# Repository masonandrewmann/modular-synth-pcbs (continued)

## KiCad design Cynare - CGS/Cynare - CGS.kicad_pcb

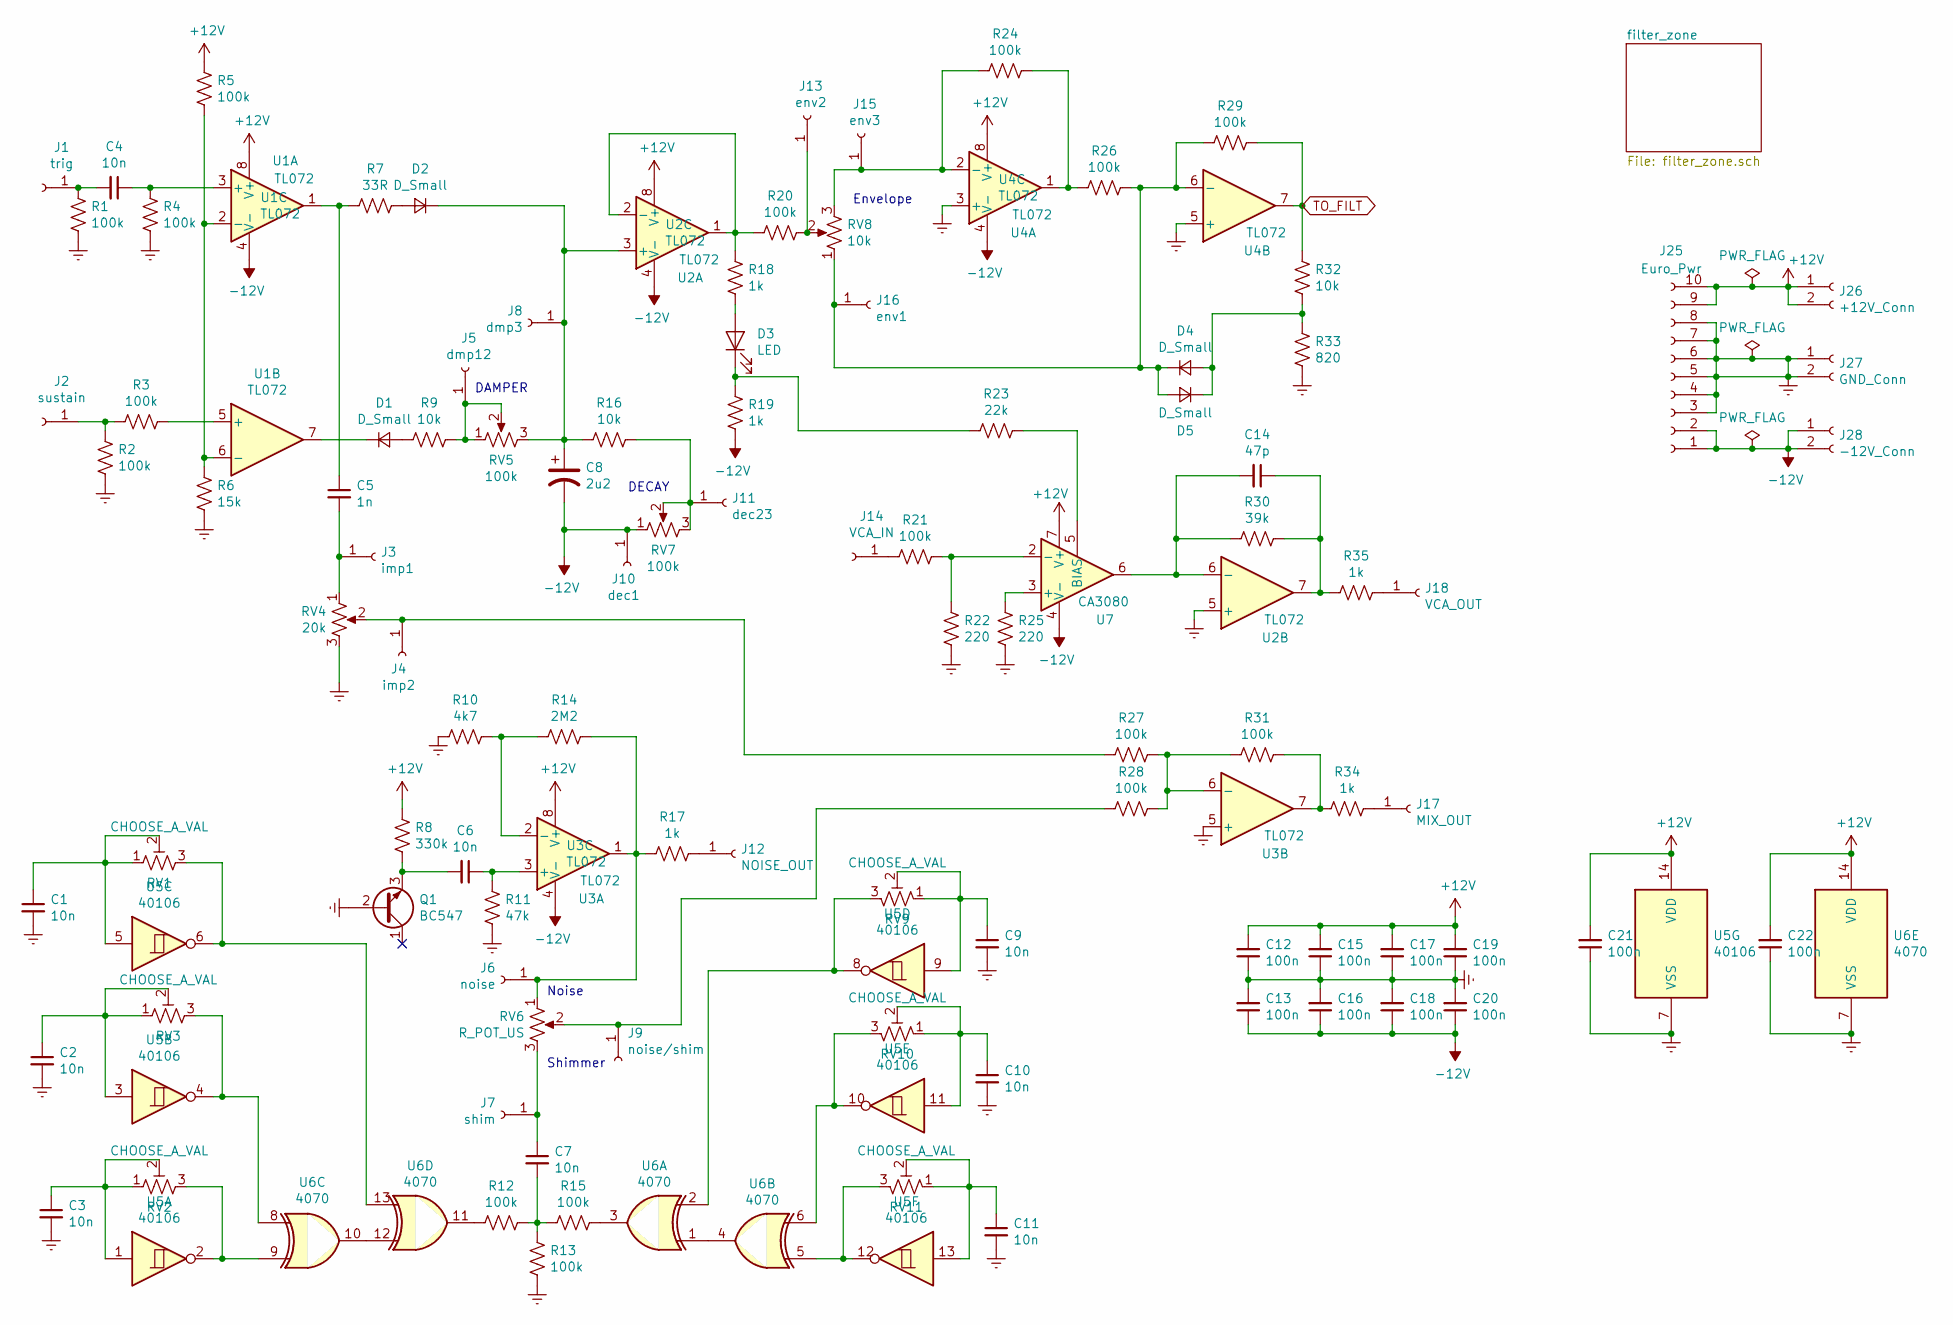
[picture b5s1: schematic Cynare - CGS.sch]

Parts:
C1, C2, C3, C4, C6, C7, C9, C10, C11: 10n; C_Rect_L7.0mm_W2.5mm_P5.00mm
C5: 1n; C_Rect_L7.0mm_W2.5mm_P5.00mm
C8: 2u2; CP_Radial_D5.0mm_P2.00mm
C12, C13, C15, C16, C17, C18, C19, C20, C21, C22: 100n; C_Rect_L7.0mm_W2.5mm_P5.00mm
C14: 47p; C_Rect_L7.0mm_W2.5mm_P5.00mm
D1, D2, D4, D5: D_Small; D_T-1_P5.08mm_Horizontal
D3: LED; LED_D4.0mm
J1: trig; SolderWirePad_1x01_Drill1mm
J2: sustain; SolderWirePad_1x01_Drill1mm
J3: imp1; SolderWirePad_1x01_Drill1mm
J4: imp2; SolderWirePad_1x01_Drill1mm
J5: dmp12; SolderWirePad_1x01_Drill1mm
J6: noise; SolderWirePad_1x01_Drill1mm
J7: shim; SolderWirePad_1x01_Drill1mm
J8: dmp3; SolderWirePad_1x01_Drill1mm
J9: noise/shim; SolderWirePad_1x01_Drill1mm
J10: dec1; SolderWirePad_1x01_Drill1mm
J11: dec23; SolderWirePad_1x01_Drill1mm
J12: NOISE_OUT; SolderWirePad_1x01_Drill1mm
J13: env2; SolderWirePad_1x01_Drill1mm
J14: VCA_IN; SolderWirePad_1x01_Drill1mm
J15: env3; SolderWirePad_1x01_Drill1mm
J16: env1; SolderWirePad_1x01_Drill1mm
J17: MIX_OUT; SolderWirePad_1x01_Drill1mm
J18: VCA_OUT; SolderWirePad_1x01_Drill1mm
J25: Euro_Pwr; IDC-Header_2x05_P2.54mm_Vertical
J26: +12V_Conn; SolderWirePad_1x02_P3.81mm_Drill1mm
J27: GND_Conn; SolderWirePad_1x02_P3.81mm_Drill1mm
J28: -12V_Conn; SolderWirePad_1x02_P3.81mm_Drill1mm
Q1: BC547; TO-92_Inline_Wide
R1, R2, R3, R4, R5, R12, R13, R15, R20, R21, R24, R26, R27, R28, R29, R31: 100k; R_Axial_DIN0207_L6.3mm_D2.5mm_P7.62mm_Horizontal
R6: 15k; R_Axial_DIN0207_L6.3mm_D2.5mm_P7.62mm_Horizontal
R7: 33R; R_Axial_DIN0207_L6.3mm_D2.5mm_P7.62mm_Horizontal
R8: 330k; R_Axial_DIN0207_L6.3mm_D2.5mm_P7.62mm_Horizontal
R9, R16, R32: 10k; R_Axial_DIN0207_L6.3mm_D2.5mm_P7.62mm_Horizontal
R10: 4k7; R_Axial_DIN0207_L6.3mm_D2.5mm_P7.62mm_Horizontal
R11: 47k; R_Axial_DIN0207_L6.3mm_D2.5mm_P7.62mm_Horizontal
R14: 2M2; R_Axial_DIN0207_L6.3mm_D2.5mm_P7.62mm_Horizontal
R17, R18, R19, R34, R35: 1k; R_Axial_DIN0207_L6.3mm_D2.5mm_P7.62mm_Horizontal
R22, R25: 220; R_Axial_DIN0207_L6.3mm_D2.5mm_P7.62mm_Horizontal
R23: 22k; R_Axial_DIN0207_L6.3mm_D2.5mm_P7.62mm_Horizontal
R30: 39k; R_Axial_DIN0207_L6.3mm_D2.5mm_P7.62mm_Horizontal
R33: 820; R_Axial_DIN0207_L6.3mm_D2.5mm_P7.62mm_Horizontal
RV1, RV2, RV3, RV9, RV10, RV11: CHOOSE_A_VAL; Potentiometer_Runtron_RM-065_Vertical
RV4: 20k
RV5, RV7: 100k
RV6: R_POT_US
RV8: 10k
U1, U2, U3, U4: TL072; DIP-8_W7.62mm_Socket
U5: 40106; DIP-14_W7.62mm_Socket
U6: 4070; DIP-14_W7.62mm_Socket
U7: CA3080; DIP-8_W7.62mm_Socket

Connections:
+12V: C12.2, C15.2, C17.2, C19.2, C21.2, C22.2, J25.9, J25.10, J26.1, J26.2, R5.1, R8.2, U1.8 (V+), U2.8 (V+), U3.8 (V+), U4.8 (V+), U5.14 (VDD), U6.14 (VDD), U7.7 (V+); also elsewhere on the board
-12V: C8.2, C13.1, C16.1, C18.1, C20.1, J10.1, J25.1, J25.2, J28.1, J28.2, R19.1, RV7.1, U1.4 (V-), U2.4 (V-), U3.4 (V-), U4.4 (V-), U7.4 (V-); also elsewhere on the board
Earth: C1.2, C2.2, C3.2, C9.2, C10.2, C11.2, C12.1, C13.2, C15.1, C16.2, C17.1, C18.2, C19.1, C20.2, C21.1, C22.1, J25.3, J25.4, J25.5, J25.6, J25.7, J25.8, J27.1, J27.2, Q1.2 (B), R1.2, R2.1, R4.2, R6.1, R10.2, R11.1, R13.1, R22.1, R25.1, R33.1, RV4.3, U2.5 (+), U3.5 (+), U4.3 (+), U4.5 (+), U5.7 (VSS), U6.7 (VSS); also elsewhere on the board
unnamed: C1.1, RV1.1, RV1.2, U5.5
unnamed: C2.1, RV3.1, RV3.2, U5.3
unnamed: C3.1, RV2.1, RV2.2, U5.1
unnamed: C4.1, R4.1, U1.3 (+)
unnamed: C4.2, J1.1, R1.1
unnamed: C5.1, R7.2, U1.1
unnamed: C5.2, J3.1, RV4.1
unnamed: C6.1, R11.2, U3.3 (+)
unnamed: C6.2, Q1.3 (E), R8.1
unnamed: C7.1, J7.1, RV6.3
unnamed: C7.2, R12.1, R13.2, R15.1
unnamed: C8.1, D2.1 (K), J8.1, R16.2, RV5.3, U2.3 (+)
unnamed: C9.1, RV9.1, RV9.2, U5.9
unnamed: C10.1, RV10.1, RV10.2, U5.11
unnamed: C11.1, RV11.1, RV11.2, U5.13
unnamed: C14.1, R30.2, R35.1, U2.7
unnamed: C14.2, R30.1, U2.6 (-), U7.6
unnamed: D1.1 (K), U1.7
unnamed: D1.2 (A), R9.2
unnamed: D2.2 (A), R7.1
unnamed: D3.1 (K), R19.2, R23.1
unnamed: D3.2 (A), R18.1
unnamed: D4.1 (K), D5.2 (A), J16.1, R26.1, R29.2, RV8.1, U4.6 (-)
unnamed: D4.2 (A), D5.1 (K), R32.1, R33.2
unnamed: J2.1, R2.2, R3.2
unnamed: J4.1, R27.1, RV4.2
unnamed: J5.1, R9.1, RV5.1, RV5.2
unnamed: J6.1, R14.1, R17.2, RV6.1, U3.1
unnamed: J9.1, R28.1, RV6.2
unnamed: J11.1, R16.1, RV7.2, RV7.3
unnamed: J12.1, R17.1
unnamed: J13.1, R20.1, RV8.2
unnamed: J14.1, R21.1
unnamed: J15.1, R24.2, RV8.3, U4.2 (-)
unnamed: J17.1, R34.2
unnamed: J18.1, R35.2
unnamed: R3.1, U1.5 (+)
unnamed: R5.2, R6.2, U1.2 (-), U1.6 (-)
unnamed: R10.1, R14.2, U3.2 (-)
unnamed: R12.2, U6.11
unnamed: R15.2, U6.3
unnamed: R18.2, R20.2, U2.1, U2.2 (-)
unnamed: R21.2, R22.2, U7.2 (-)
unnamed: R23.2, U7.5 (BIAS)
unnamed: R24.1, R26.2, U4.1
unnamed: R25.2, U7.3 (+)
unnamed: R27.2, R28.2, R31.1, U3.6 (-)
unnamed: R31.2, R34.1, U3.7
unnamed: RV1.3, U5.6, U6.13
unnamed: RV2.3, U5.2, U6.9
unnamed: RV3.3, U5.4, U6.8
unnamed: RV9.3, U5.8, U6.2
unnamed: RV10.3, U5.10, U6.6
unnamed: RV11.3, U5.12, U6.5
unnamed: U6.1, U6.4
unnamed: U6.10, U6.12
TO_FILT: R29.1, R32.2, U4.7; also elsewhere on the board

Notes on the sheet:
DAMPER
DECAY
Noise
Shimmer
Envelope

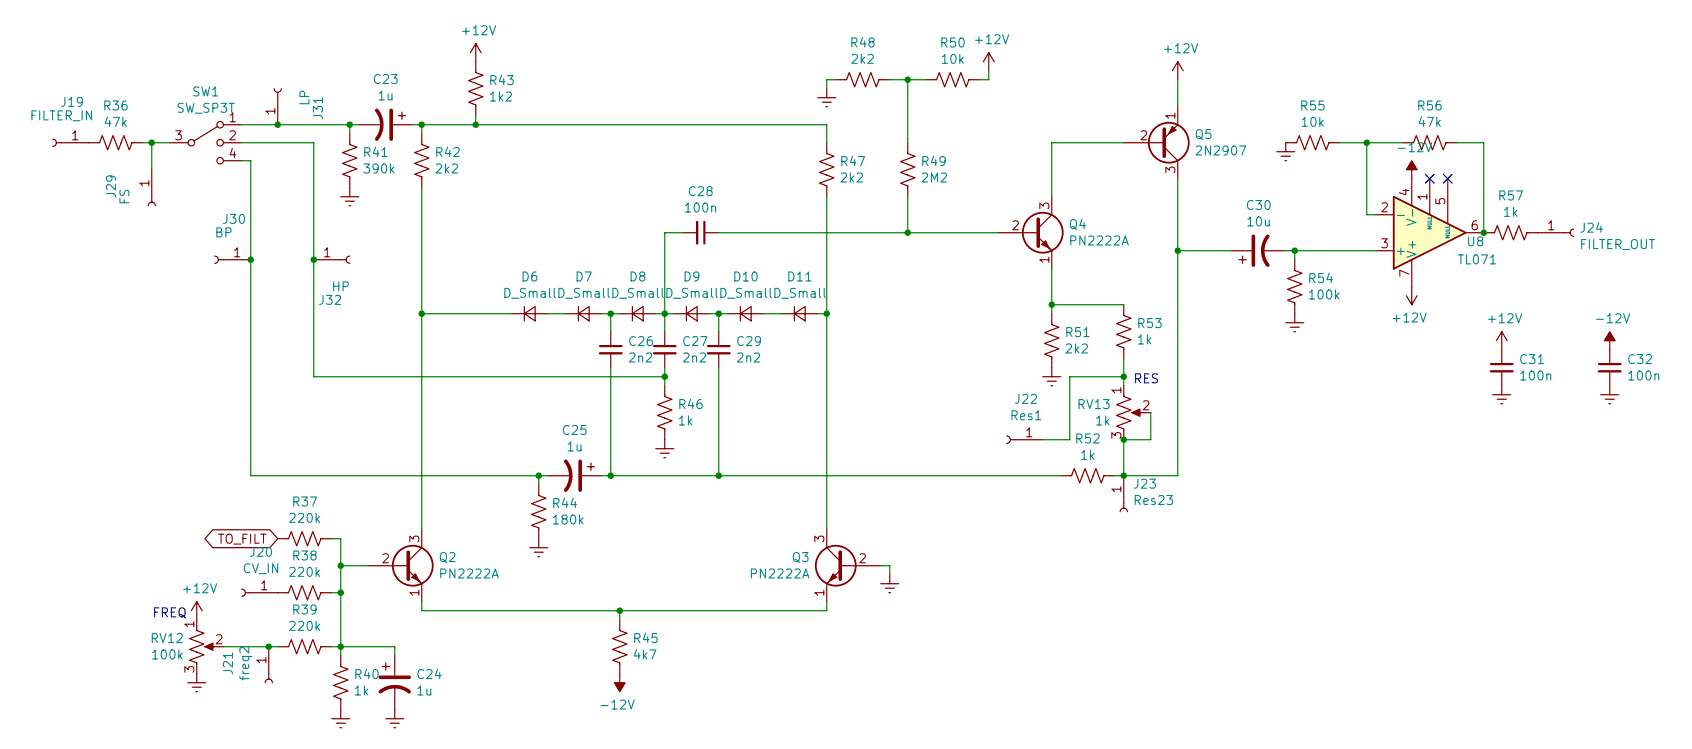
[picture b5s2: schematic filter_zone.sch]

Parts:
C23, C24, C25: 1u; CP_Radial_D5.0mm_P2.50mm
C26, C27, C29: 2n2; C_Rect_L7.0mm_W2.5mm_P5.00mm
C28: 100n; C_Rect_L7.0mm_W2.5mm_P5.00mm
C30: 10u; CP_Radial_D5.0mm_P2.50mm
C31, C32: 100n; C_0603_1608Metric_Pad1.05x0.95mm_HandSolder
D6, D7, D8, D9, D10, D11: D_Small; D_T-1_P5.08mm_Horizontal
J19: FILTER_IN; SolderWirePad_1x01_Drill1mm
J20: CV_IN; SolderWirePad_1x01_Drill1mm
J21: freq2; SolderWirePad_1x01_Drill1mm
J22: Res1; SolderWirePad_1x01_Drill1mm
J23: Res23; SolderWirePad_1x01_Drill1mm
J24: FILTER_OUT; SolderWirePad_1x01_Drill1mm
J29: FS; SolderWirePad_1x01_Drill1mm
J30: BP; SolderWirePad_1x01_Drill1mm
J31: LP; SolderWirePad_1x01_Drill1mm
J32: HP; SolderWirePad_1x01_Drill1mm
Q2, Q3, Q4: PN2222A; TO-92_Inline_Wide
Q5: 2N2907; TO-92_Inline_Wide
R36, R56: 47k; R_Axial_DIN0207_L6.3mm_D2.5mm_P7.62mm_Horizontal
R37, R38, R39: 220k; R_Axial_DIN0207_L6.3mm_D2.5mm_P7.62mm_Horizontal
R40, R46, R52, R53, R57: 1k; R_Axial_DIN0207_L6.3mm_D2.5mm_P7.62mm_Horizontal
R41: 390k; R_Axial_DIN0207_L6.3mm_D2.5mm_P7.62mm_Horizontal
R42, R47, R48, R51: 2k2; R_Axial_DIN0207_L6.3mm_D2.5mm_P7.62mm_Horizontal
R43: 1k2; R_Axial_DIN0207_L6.3mm_D2.5mm_P7.62mm_Horizontal
R44: 180k; R_Axial_DIN0207_L6.3mm_D2.5mm_P7.62mm_Horizontal
R45: 4k7; R_Axial_DIN0207_L6.3mm_D2.5mm_P7.62mm_Horizontal
R49: 2M2; R_Axial_DIN0207_L6.3mm_D2.5mm_P7.62mm_Horizontal
R50, R55: 10k; R_Axial_DIN0207_L6.3mm_D2.5mm_P7.62mm_Horizontal
R54: 100k; R_Axial_DIN0207_L6.3mm_D2.5mm_P7.62mm_Horizontal
RV12: 100k
RV13: 1k
SW1: SW_SP3T
U8: TL071; DIP-8_W7.62mm_Socket

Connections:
+12V: C31.1, Q5.1 (E), R43.2, R50.2, RV12.1, U8.7 (V+); also elsewhere on the board
-12V: C32.1, R45.1, U8.4 (V-); also elsewhere on the board
Earth: C24.2, C31.2, C32.2, Q3.2 (B), R40.2, R41.1, R44.1, R46.1, R48.1, R51.2, R54.2, R55.2, RV12.3; also elsewhere on the board
unnamed: C23.1, R42.2, R43.1, R47.2
unnamed: C23.2, J31.1, R41.2, SW1.1
unnamed: C24.1, Q2.2 (B), R37.2, R38.2, R39.2, R40.1
unnamed: C25.1, C26.2, C29.2, R52.2
unnamed: C25.2, J30.1, R44.2, SW1.4
unnamed: C26.1, D7.2 (A), D8.1 (K)
unnamed: C27.1, C28.2, D8.2 (A), D9.1 (K)
unnamed: C27.2, J32.1, R46.2, SW1.2
unnamed: C28.1, Q4.2 (B), R49.1
unnamed: C29.1, D9.2 (A), D10.1 (K)
unnamed: C30.1, J23.1, Q5.3 (C), R52.1, RV13.2, RV13.3
unnamed: C30.2, R54.1, U8.3 (+)
unnamed: D6.1 (K), Q2.3 (C), R42.1
unnamed: D6.2 (A), D7.1 (K)
unnamed: D10.2 (A), D11.1 (K)
unnamed: D11.2 (A), Q3.3 (C), R47.1
unnamed: J19.1, R36.2
unnamed: J20.1, R38.1
unnamed: J21.1, R39.1, RV12.2
unnamed: J22.1, R53.2, RV13.1
unnamed: J24.1, R57.1
unnamed: J29.1, R36.1, SW1.3
unnamed: Q2.1 (E), Q3.1 (E), R45.2
unnamed: Q4.1 (E), R51.1, R53.1
unnamed: Q4.3 (C), Q5.2 (B)
unnamed: R48.2, R49.2, R50.1
unnamed: R55.1, R56.2, U8.2 (-)
unnamed: R56.1, R57.2, U8.6
TO_FILT: R37.1; also elsewhere on the board

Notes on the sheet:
RES
FREQ

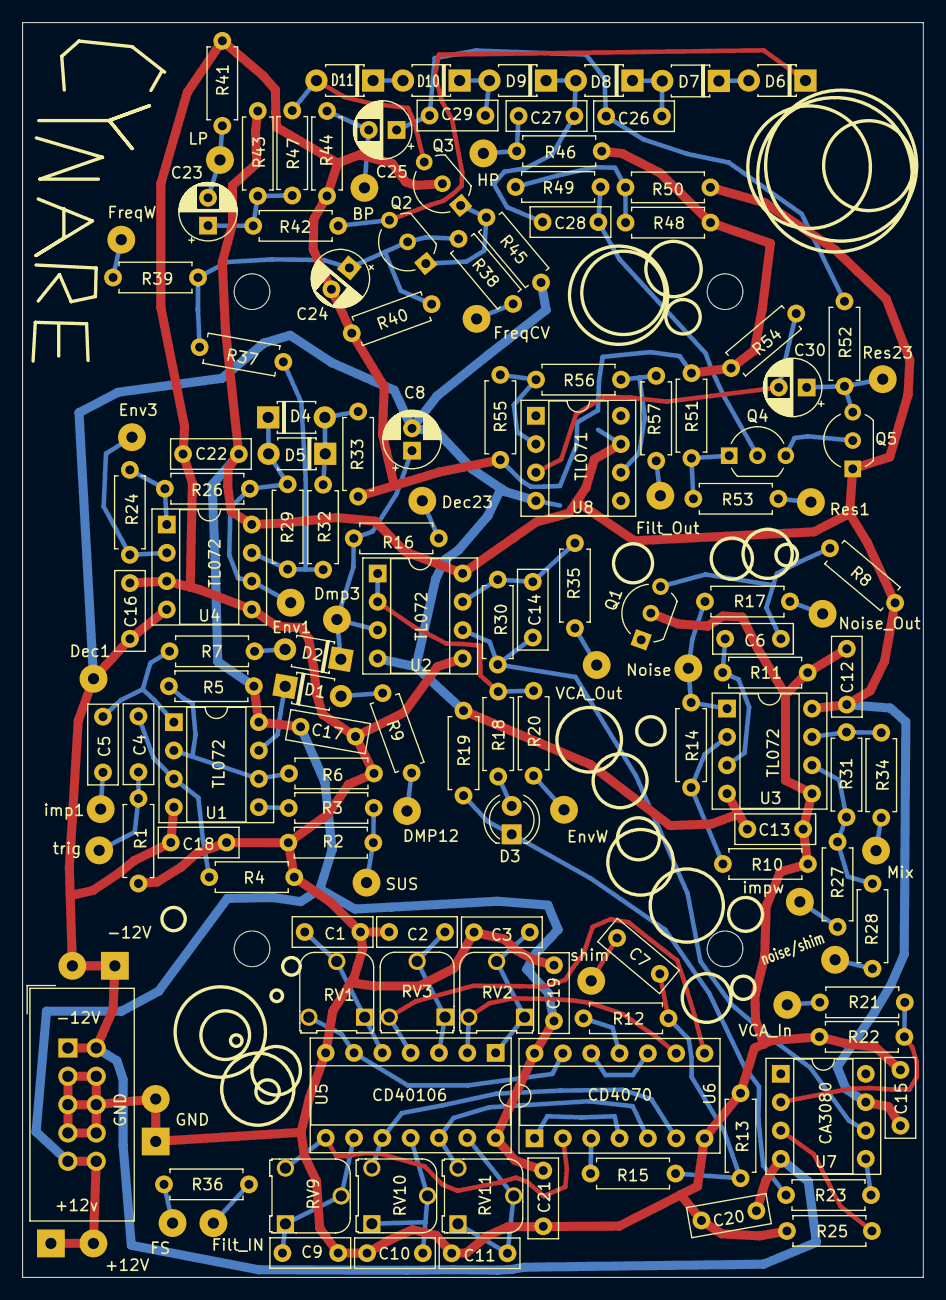
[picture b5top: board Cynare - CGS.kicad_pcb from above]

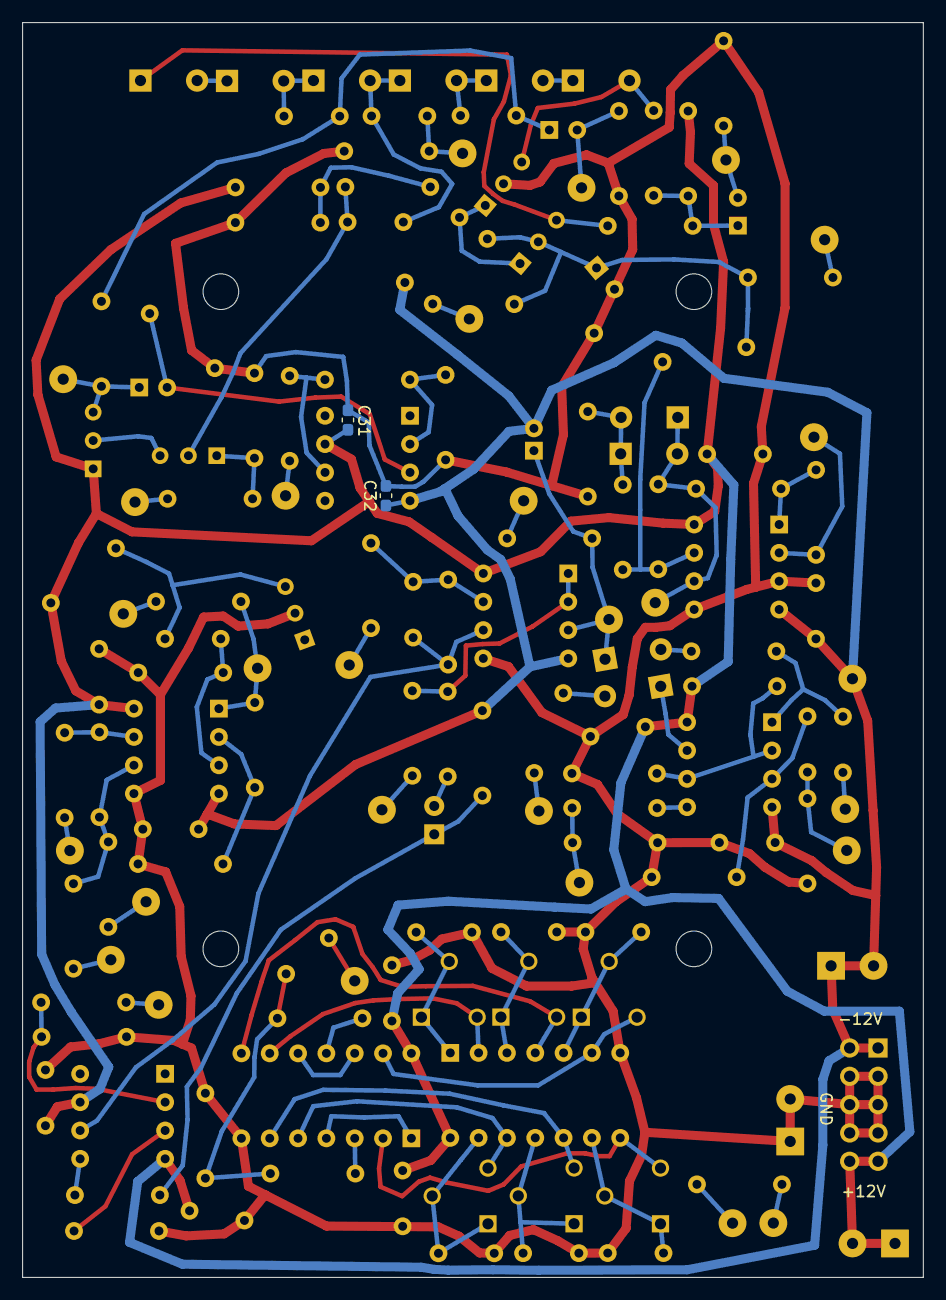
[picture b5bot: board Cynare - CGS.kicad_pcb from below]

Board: 2 copper layers, 80.8 x 112.5 mm, 151 parts (2 on the bottom side), 88 nets.

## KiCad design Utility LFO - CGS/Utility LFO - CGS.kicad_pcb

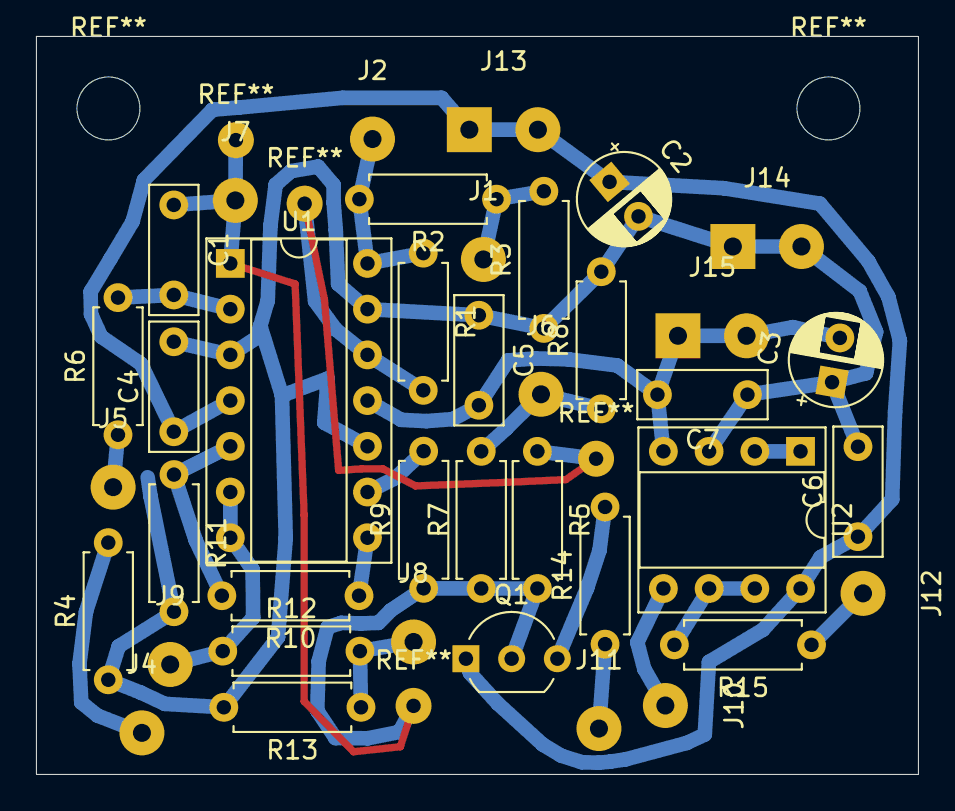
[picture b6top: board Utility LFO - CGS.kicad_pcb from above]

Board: 2 copper layers, 49.0 x 41.0 mm, 39 parts (0 on the bottom side), 22 nets.

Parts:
C1: 47n; C_Rect_L7.0mm_W2.5mm_P5.00mm
C2, C3: 10u; CP_Radial_D5.0mm_P2.50mm
C4, C5, C6, C7: 100n; C_Rect_L7.0mm_W2.5mm_P5.00mm
J1: Pulse; SolderWirePad_1x01_Drill1mm
J2: F1; SolderWirePad_1x01_Drill1mm
J4: F3; SolderWirePad_1x01_Drill1mm
J5: Shape2; SolderWirePad_1x01_Drill1mm
J6: TRI/SAW; SolderWirePad_1x01_Drill1mm
J7: Var1; SolderWirePad_1x01_Drill1mm
J8: SQU; SolderWirePad_1x01_Drill1mm
J9: Var3; SolderWirePad_1x01_Drill1mm
J10: Var2; SolderWirePad_1x01_Drill1mm
J11: LEDA; SolderWirePad_1x01_Drill1mm
J12: Vari_Out; SolderWirePad_1x01_Drill1mm
J13: +12v; SolderWirePad_1x02_P3.81mm_Drill1mm
J14: GND; SolderWirePad_1x02_P3.81mm_Drill1mm
J15: -12v; SolderWirePad_1x02_P3.81mm_Drill1mm
Q1: BC547; TO-92_Inline_Wide
R1: 150k; R_Axial_DIN0207_L6.3mm_D2.5mm_P7.62mm_Horizontal
R2: 2k2; R_Axial_DIN0207_L6.3mm_D2.5mm_P7.62mm_Horizontal
R3, R7, R8, R12, R13, R14, R15: 1k; R_Axial_DIN0207_L6.3mm_D2.5mm_P7.62mm_Horizontal
R4: 4k7; R_Axial_DIN0207_L6.3mm_D2.5mm_P7.62mm_Horizontal
R5, R9, R11: 100k; R_Axial_DIN0207_L6.3mm_D2.5mm_P7.62mm_Horizontal
R6: 10k; R_Axial_DIN0207_L6.3mm_D2.5mm_P7.62mm_Horizontal
R10: 47k; R_Axial_DIN0207_L6.3mm_D2.5mm_P7.62mm_Horizontal
U1: TL074; DIP-14_W7.62mm_Socket
U2: TL072; DIP-8_W7.62mm_Socket

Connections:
+12V: C2.1, C4.1, C6.1, J13.1, J13.2, Q1.1, U1.4, U2.8
-12V: C3.2, C5.2, C7.2, J15.1, J15.2, U1.11, U2.4
Earth: C2.2, C3.1, C4.2, C5.1, C6.2, C7.1, J14.1, J14.2, R3.1, R4.1, R8.2, R11.2, R13.2, U1.3, U1.10, U1.13, U2.3
unnamed: C1.1, J7.1, Q1.2, R5.2, R7.1, R9.1, U1.1
unnamed: C1.2, R6.2, U1.2
unnamed: J1.1, R2.1, R3.2
unnamed: J2.1, R1.1, R2.2, U1.14
unnamed: J4.1, R4.2
unnamed: J5.1, R6.1
unnamed: J6.1, R7.2, R8.1
unnamed: J8.1, R12.2, R13.1
unnamed: J9.1, R12.1, U1.6, U1.7
unnamed: J10.1, U2.5
unnamed: J11.1, R14.1
unnamed: J12.1, R15.1
unnamed: Q1.3, R14.2
unnamed: R1.2, R5.1, U1.12
unnamed: R9.2, U1.9
unnamed: R10.1, U1.8
unnamed: R10.2, R11.1, U1.5
unnamed: R15.2, U2.6, U2.7
unnamed: U2.1, U2.2

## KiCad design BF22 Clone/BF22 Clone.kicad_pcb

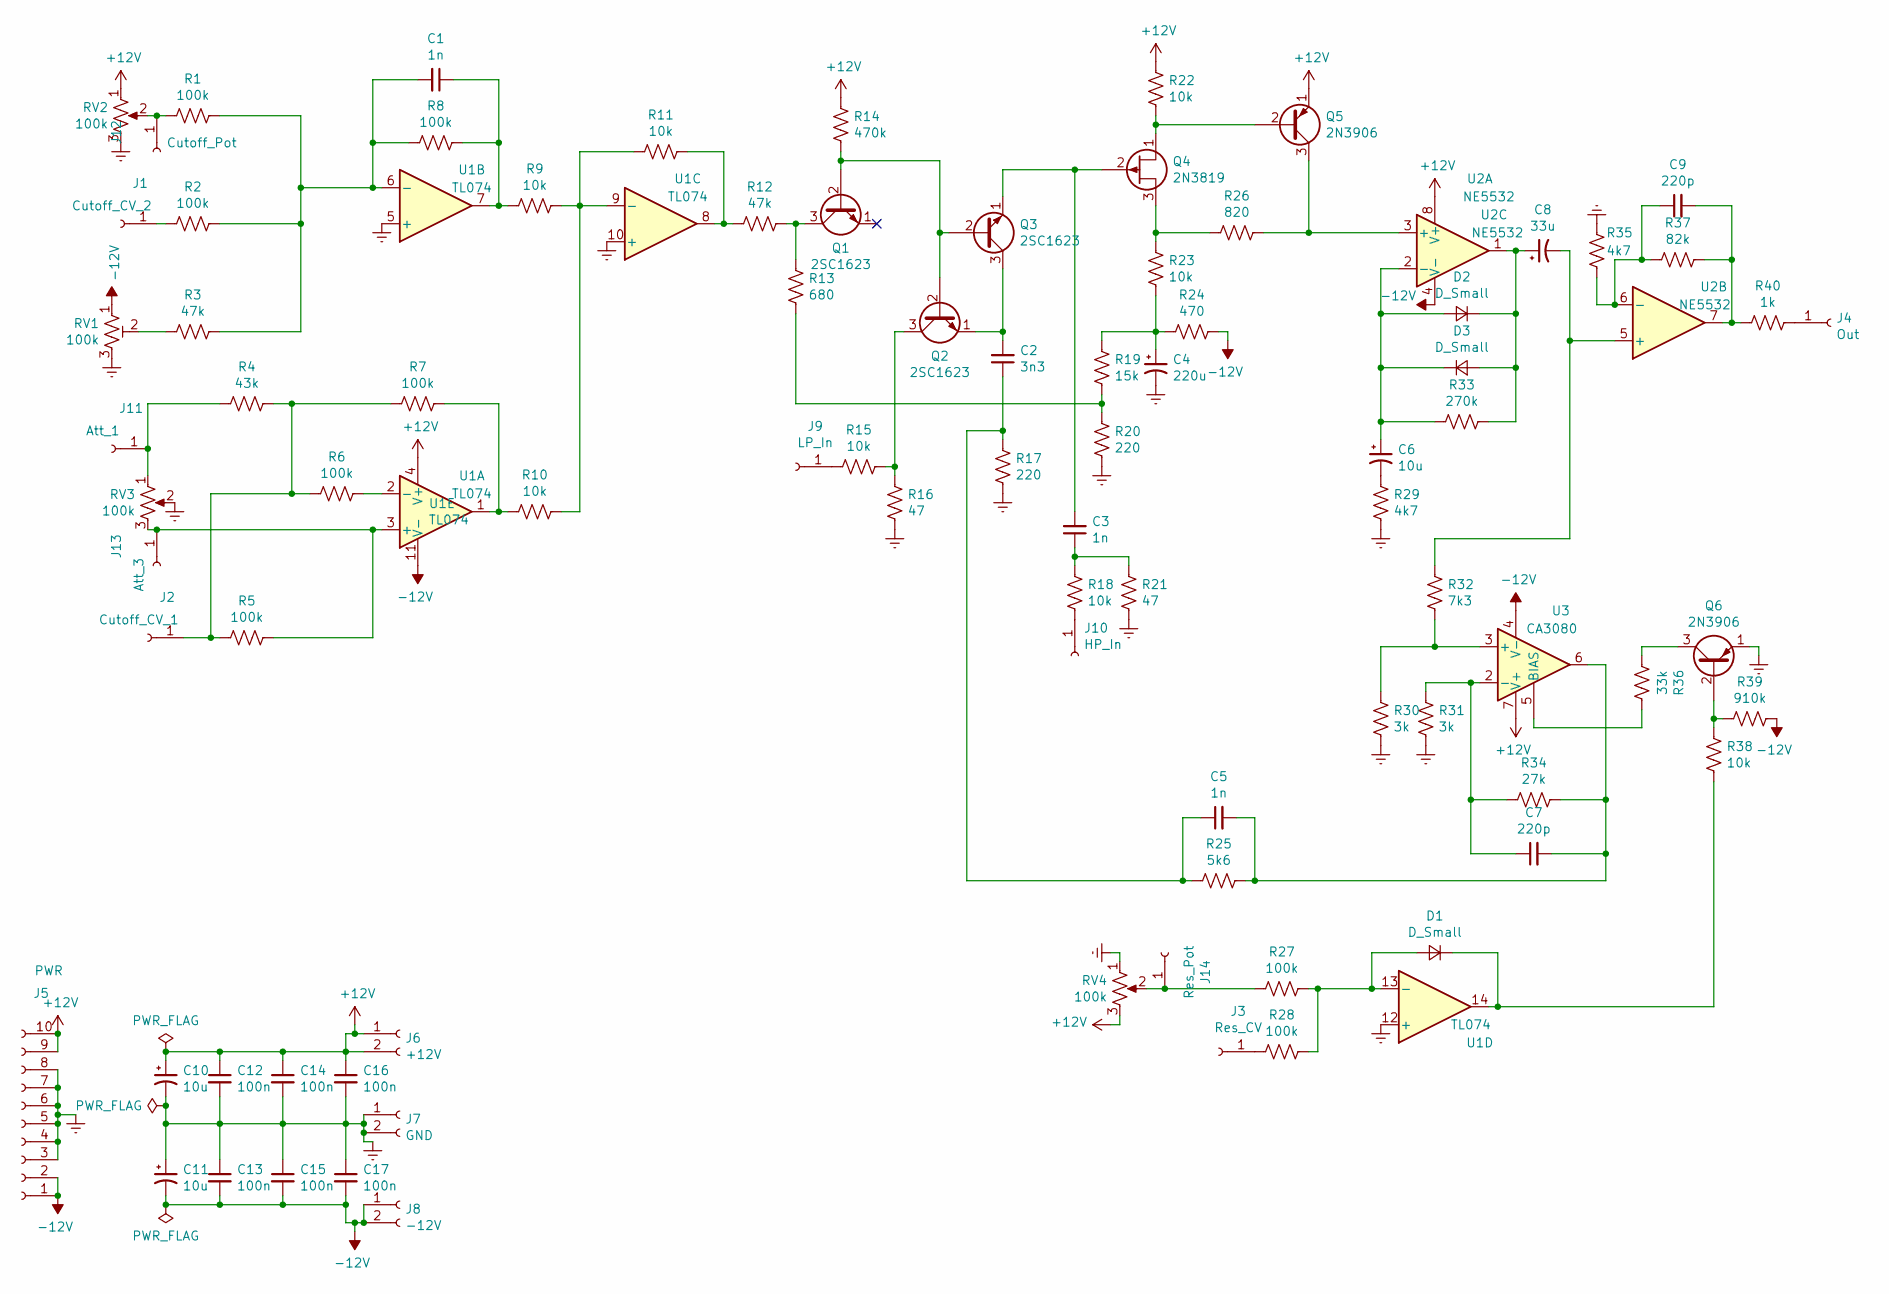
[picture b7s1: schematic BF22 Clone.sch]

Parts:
C1, C3, C5: 1n; C_0603_1608Metric_Pad1.05x0.95mm_HandSolder
C2: 3n3; C_0603_1608Metric_Pad1.05x0.95mm_HandSolder
C4: 220u; CP_Elec_6.3x5.4
C6, C10, C11: 10u; CP_Elec_4x5.4
C7, C9: 220p; C_0603_1608Metric_Pad1.05x0.95mm_HandSolder
C8: 33u; CP_Elec_5x5.7
C12, C13, C14, C15, C16, C17: 100n; C_0603_1608Metric_Pad1.05x0.95mm_HandSolder
D1, D2, D3: D_Small; D_SOD-323F
J1: Cutoff_CV_2; SolderWirePad_1x01_Drill1mm
J2: Cutoff_CV_1; SolderWirePad_1x01_Drill1mm
J3: Res_CV; SolderWirePad_1x01_Drill1mm
J4: Out; SolderWirePad_1x01_Drill1mm
J5: PWR; IDC-Header_2x05_P2.54mm_Vertical
J6: +12V; SolderWirePad_1x02_P3.81mm_Drill1mm
J7: GND; SolderWirePad_1x02_P3.81mm_Drill1mm
J8: -12V; SolderWirePad_1x02_P3.81mm_Drill1mm
J9: LP_In; SolderWirePad_1x01_Drill1mm
J10: HP_In; SolderWirePad_1x01_Drill1mm
J11: Att_1; SolderWirePad_1x01_Drill1mm
J12: Cutoff_Pot; SolderWirePad_1x01_Drill1mm
J13: Att_3; SolderWirePad_1x01_Drill1mm
J14: Res_Pot; SolderWirePad_1x01_Drill1mm
Q1, Q2, Q3: 2SC1623; TO-92L_Inline_Wide
Q4: 2N3819; TO-92L_Inline_Wide
Q5, Q6: 2N3906; TO-92_Inline_Wide
R1, R2, R5, R6, R7, R8, R27, R28: 100k; R_0603_1608Metric_Pad1.05x0.95mm_HandSolder
R3, R12: 47k; R_0603_1608Metric_Pad1.05x0.95mm_HandSolder
R4: 43k; R_0603_1608Metric_Pad1.05x0.95mm_HandSolder
R9, R10, R11, R15, R18, R22, R23, R38: 10k; R_0603_1608Metric_Pad1.05x0.95mm_HandSolder
R13: 680; R_0603_1608Metric_Pad1.05x0.95mm_HandSolder
R14: 470k; R_0603_1608Metric_Pad1.05x0.95mm_HandSolder
R16, R21: 47; R_0603_1608Metric_Pad1.05x0.95mm_HandSolder
R17, R20: 220; R_0603_1608Metric_Pad1.05x0.95mm_HandSolder
R19: 15k; R_0603_1608Metric_Pad1.05x0.95mm_HandSolder
R24: 470; R_0603_1608Metric_Pad1.05x0.95mm_HandSolder
R25: 5k6; R_0603_1608Metric_Pad1.05x0.95mm_HandSolder
R26: 820; R_0603_1608Metric_Pad1.05x0.95mm_HandSolder
R29, R35: 4k7; R_0603_1608Metric_Pad1.05x0.95mm_HandSolder
R30, R31: 3k; R_0603_1608Metric_Pad1.05x0.95mm_HandSolder
R32: 7k3; R_Axial_DIN0207_L6.3mm_D2.5mm_P7.62mm_Horizontal
R33: 270k; R_0603_1608Metric_Pad1.05x0.95mm_HandSolder
R34: 27k; R_0603_1608Metric_Pad1.05x0.95mm_HandSolder
R36: 33k; R_0603_1608Metric_Pad1.05x0.95mm_HandSolder
R37: 82k; R_0603_1608Metric_Pad1.05x0.95mm_HandSolder
R39: 910k; R_0603_1608Metric_Pad1.05x0.95mm_HandSolder
R40: 1k; R_0603_1608Metric_Pad1.05x0.95mm_HandSolder
RV1: 100k; Potentiometer_Runtron_RM-065_Vertical
RV2, RV3, RV4: 100k
U1: TL074; SOIC-14_3.9x8.7mm_P1.27mm
U2: NE5532; DIP-8_W7.62mm_Socket
U3: CA3080; DIP-8_W7.62mm_Socket

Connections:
+12V: C10.1, C12.1, C14.1, C16.1, J5.9, J5.10, J6.1, J6.2, Q5.1 (E), R14.2, R22.2, RV2.1, RV4.3, U1.4 (V+), U2.8 (V+), U3.7 (V+)
-12V: C11.2, C13.2, C15.2, C17.2, J5.1, J5.2, J8.1, J8.2, R24.1, R39.2, RV1.1, U1.11 (V-), U2.4 (V-), U3.4 (V-); also elsewhere on the board
Earth: C4.2, C10.2, C11.1, C12.2, C13.1, C14.2, C15.1, C16.2, C17.1, J5.3, J5.4, J5.5, J5.6, J5.7, J5.8, J7.1, J7.2, Q6.1 (E), R16.1, R17.1, R20.1, R21.1, R29.2, R30.1, R31.1, R35.1, RV1.3, RV2.3, RV3.2, RV4.1, U1.5 (+), U1.10 (+), U1.12 (+); also elsewhere on the board
unnamed: C1.1, R8.1, R9.2, U1.7
unnamed: C1.2, R1.1, R2.1, R3.2, R8.2, U1.6 (-)
unnamed: C2.1, C5.1, R17.2, R25.1
unnamed: C2.2, Q2.1 (E), Q3.3 (C)
unnamed: C3.1, R18.2, R21.2
unnamed: C3.2, Q3.1 (E), Q4.2 (G)
unnamed: C4.1, R19.2, R23.2, R24.2
unnamed: C5.2, C7.2, R25.2, R34.1, U3.6
unnamed: C6.1, D2.2 (A), D3.1 (K), R33.1, U2.2 (-)
unnamed: C6.2, R29.1
unnamed: C7.1, R31.2, R34.2, U3.2 (-)
unnamed: C8.1, D2.1 (K), D3.2 (A), R33.2, U2.1
unnamed: C8.2, R32.2, U2.5 (+)
unnamed: C9.1, R35.2, R37.1, U2.6 (-)
unnamed: C9.2, R37.2, R40.1, U2.7
unnamed: D1.1 (K), R38.2, U1.14
unnamed: D1.2 (A), R27.2, R28.2, U1.13 (-)
unnamed: J1.1, R2.2
unnamed: J2.1, R4.1, R5.2, R6.2, R7.2
unnamed: J3.1, R28.1
unnamed: J4.1, R40.2
unnamed: J9.1, R15.1
unnamed: J10.1, R18.1
unnamed: J11.1, R4.2, RV3.1
unnamed: J12.1, R1.2, RV2.2
unnamed: J13.1, R5.1, RV3.3, U1.3 (+)
unnamed: J14.1, R27.1, RV4.2
unnamed: Q1.2 (B), Q2.2 (B), Q3.2 (B), R14.1
unnamed: Q1.3 (C), R12.1, R13.2
unnamed: Q2.3 (C), R15.2, R16.2
unnamed: Q4.1 (D), Q5.2 (B), R22.1
unnamed: Q4.3 (S), R23.1, R26.1
unnamed: Q5.3 (C), R26.2, U2.3 (+)
unnamed: Q6.2 (B), R38.1, R39.1
unnamed: Q6.3 (C), R36.1
unnamed: R3.1, RV1.2
unnamed: R6.1, U1.2 (-)
unnamed: R9.1, R10.1, R11.2, U1.9 (-)
unnamed: R7.1, R10.2, U1.1
unnamed: R11.1, R12.2, U1.8
unnamed: R13.1, R19.1, R20.2
unnamed: R30.2, R32.1, U3.3 (+)
unnamed: R36.2, U3.5 (BIAS)

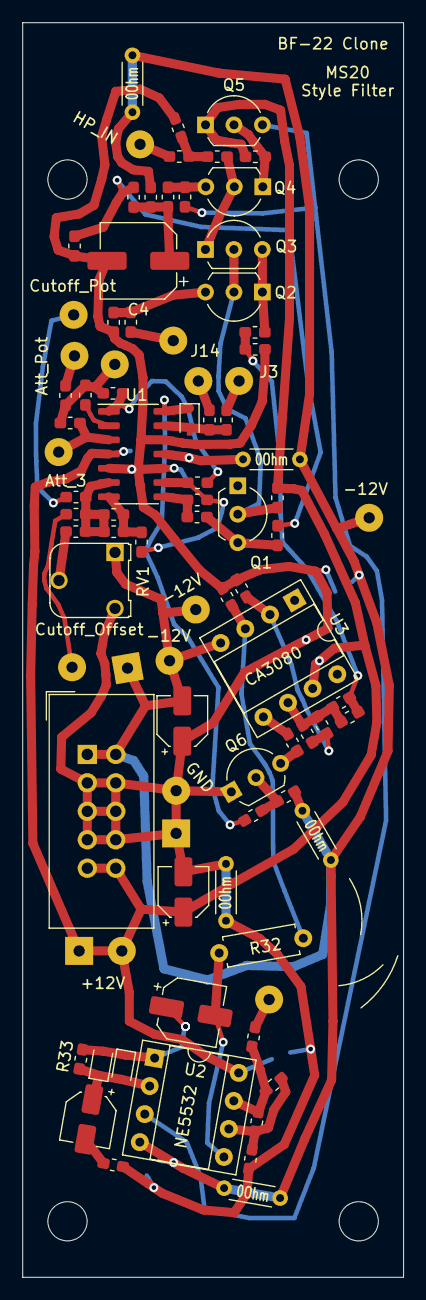
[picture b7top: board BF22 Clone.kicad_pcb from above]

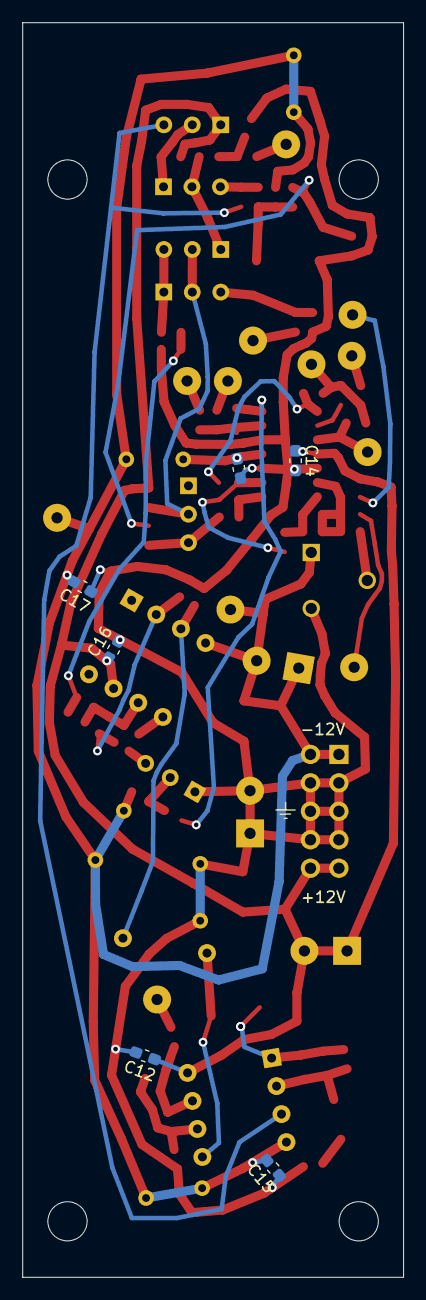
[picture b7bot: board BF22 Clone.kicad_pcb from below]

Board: 2 copper layers, 34.0 x 112.0 mm, 91 parts (6 on the bottom side), 46 nets.

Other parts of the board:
0Ohm, 0Ohm#2, 0Ohm#3, 0Ohm#4, 0Ohm#5: R_Axial_DIN0204_L3.6mm_D1.6mm_P5.08mm_Horizontal
-12V, -12V#2: SolderWirePad_1x01_Drill1mm

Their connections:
-12V: 0Ohm.1, 0Ohm.2, 0Ohm#3.1, 0Ohm#3.2, 0Ohm#4.1, 0Ohm#4.2, 0Ohm#5.1, 0Ohm#5.2, -12V.1, -12V#2.1; also elsewhere on the board
Earth: 0Ohm#2.1, 0Ohm#2.2; also elsewhere on the board

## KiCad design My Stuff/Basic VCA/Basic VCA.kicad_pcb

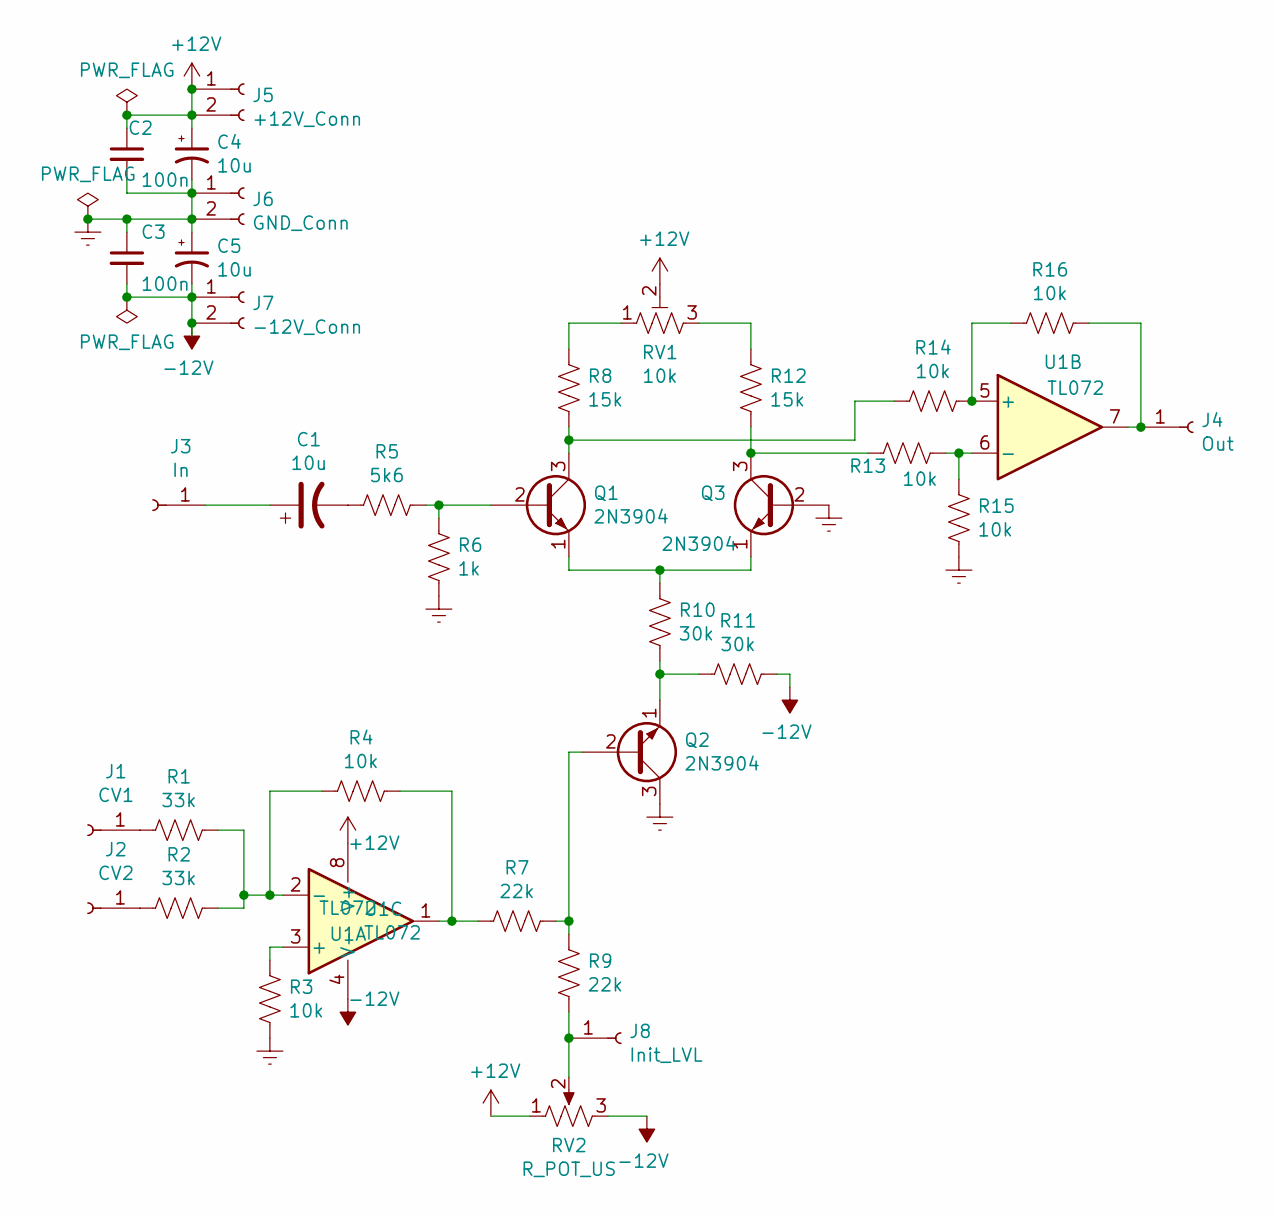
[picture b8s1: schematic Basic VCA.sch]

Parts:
C1, C4, C5: 10u; CP_Radial_D5.0mm_P2.0mm_Bigger_Holes
C2, C3: 100n; C_Rect_L7.0mm_W2.5mm_P5.00mm
J1: CV1; SolderWirePad_1x01_Drill1mm
J2: CV2; SolderWirePad_1x01_Drill1mm
J3: In; SolderWirePad_1x01_Drill1mm
J4: Out; SolderWirePad_1x01_Drill1mm
J5: +12V_Conn; SolderWirePad_1x02_P3.81mm_Drill1mm
J6: GND_Conn; SolderWirePad_1x02_P3.81mm_Drill1mm
J7: -12V_Conn; SolderWirePad_1x02_P3.81mm_Drill1mm
J8: Init_LVL; SolderWirePad_1x01_Drill1mm
Q1, Q2, Q3: 2N3904; TO-92_Inline_Wide
R1, R2: 33k; R_Axial_DIN0207_L6.3mm_D2.5mm_P7.62mm_Horizontal
R3, R4, R13, R14, R15, R16: 10k; R_Axial_DIN0207_L6.3mm_D2.5mm_P7.62mm_Horizontal
R5: 5k6; R_Axial_DIN0207_L6.3mm_D2.5mm_P7.62mm_Horizontal
R6: 1k; R_Axial_DIN0207_L6.3mm_D2.5mm_P7.62mm_Horizontal
R7, R9: 22k; R_Axial_DIN0207_L6.3mm_D2.5mm_P7.62mm_Horizontal
R8, R12: 15k; R_Axial_DIN0207_L6.3mm_D2.5mm_P7.62mm_Horizontal
R10, R11: 30k; R_Axial_DIN0207_L6.3mm_D2.5mm_P7.62mm_Horizontal
RV1: 10k; Potentiometer_Runtron_RM-065_Vertical
RV2: R_POT_US
U1: TL072; DIP-8_W7.62mm_Socket

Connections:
+12V: C2.1, C4.1, J5.1, J5.2, RV1.2, RV2.1, U1.8 (V+)
-12V: C3.2, C5.2, J7.1, J7.2, R11.2, RV2.3, U1.4 (V-)
Earth: C2.2, C3.1, C4.2, C5.1, J6.1, J6.2, Q2.3 (C), Q3.2 (B), R3.1, R6.1, R15.1
unnamed: C1.1, J3.1
unnamed: C1.2, R5.2
unnamed: J1.1, R1.2
unnamed: J2.1, R2.2
unnamed: J4.1, R16.1, U1.7
unnamed: J8.1, R9.1, RV2.2
unnamed: Q1.1 (E), Q3.1 (E), R10.2
unnamed: Q1.2 (B), R5.1, R6.2
unnamed: Q1.3 (C), R8.1, R14.2
unnamed: Q2.1 (E), R10.1, R11.1
unnamed: Q2.2 (B), R7.1, R9.2
unnamed: Q3.3 (C), R12.1, R13.2
unnamed: R1.1, R2.1, R4.2, U1.2 (-)
unnamed: R3.2, U1.3 (+)
unnamed: R4.1, R7.2, U1.1
unnamed: R8.2, RV1.1
unnamed: R12.2, RV1.3
unnamed: R13.1, R15.2, U1.6 (-)
unnamed: R14.1, R16.2, U1.5 (+)
